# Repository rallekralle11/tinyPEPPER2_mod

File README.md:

# tinyPEPPER2 -- a tiny and lightweight 4in1 BLHeli_S ESC -- 2S edition, and modified

My intent is to modify this to become a single or double ESC for compact aircraft or battlebot use.
Original is of course by https://github.com/fishpepper

This work is published under the CERN open hardware license v1.2. 
Feel free to use the design - but make sure to give proper credit 
and release all modifications under the same license! 
See LICENSE.txt for details!

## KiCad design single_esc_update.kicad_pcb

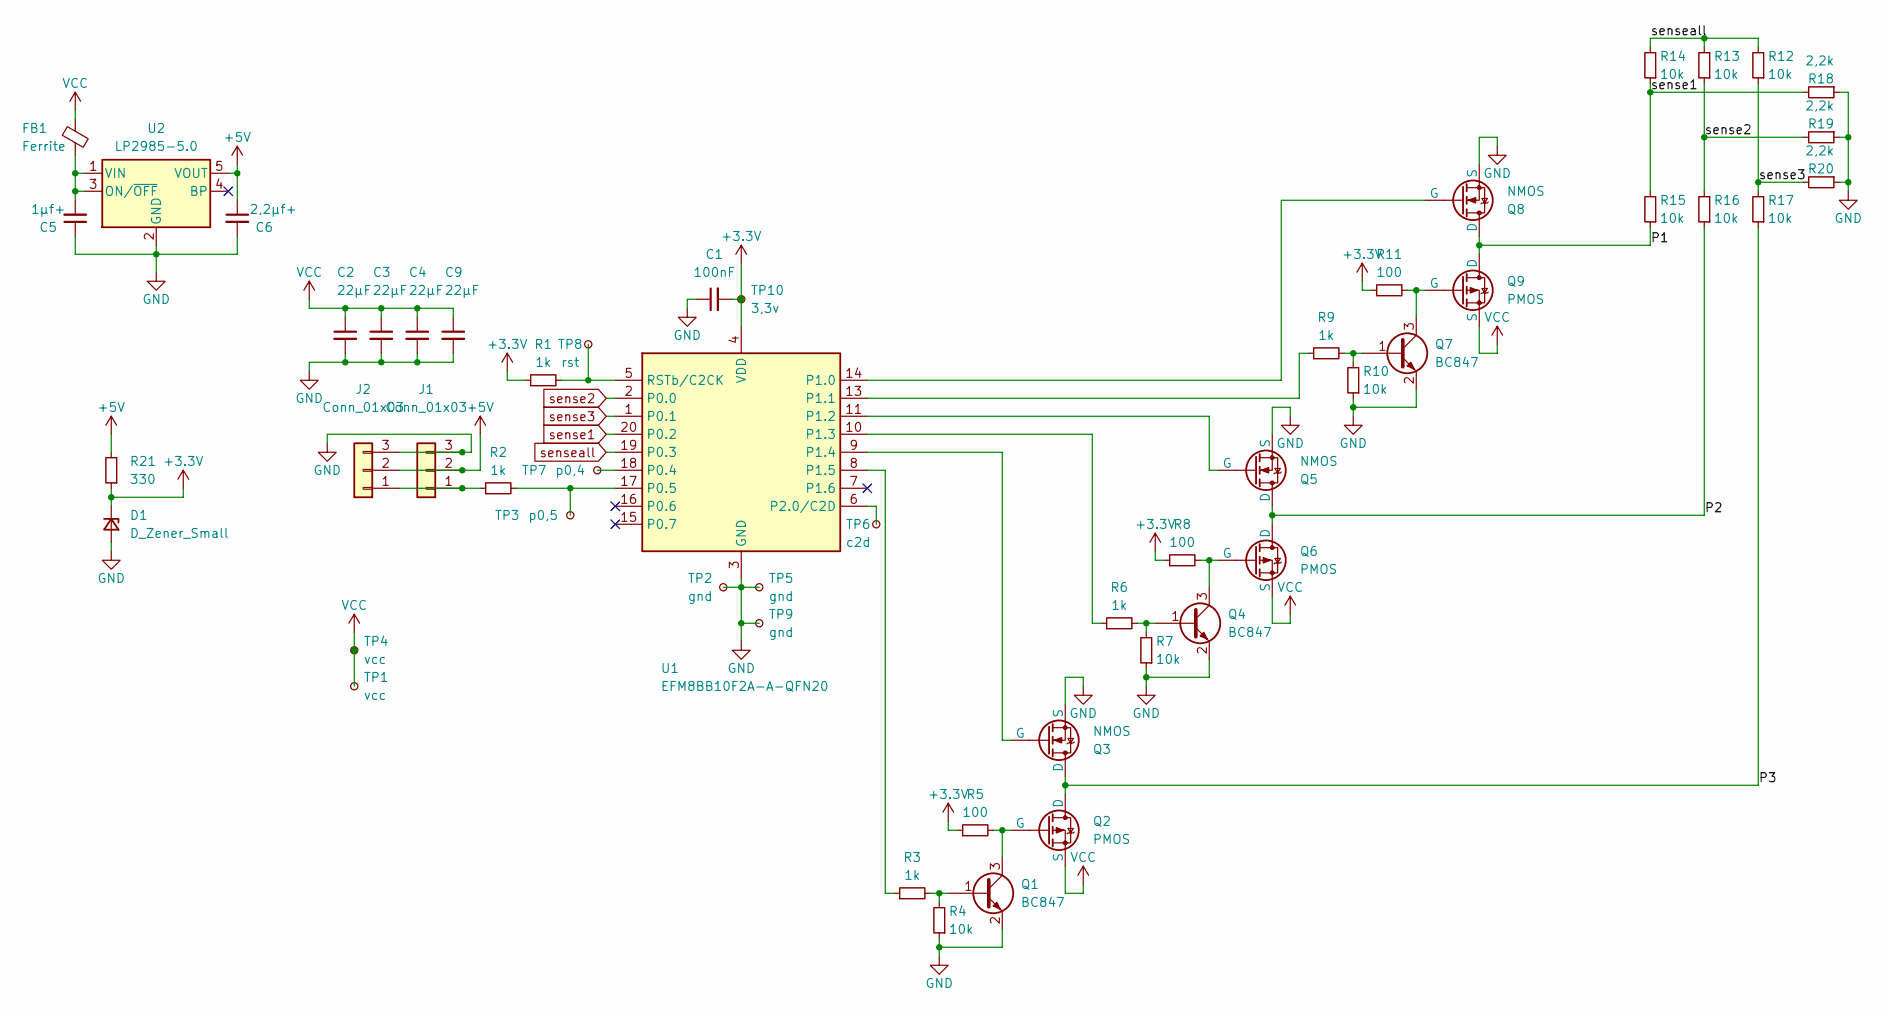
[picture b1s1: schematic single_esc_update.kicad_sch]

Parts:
C1: 100nF; C_0402_1005Metric
C2, C3, C4, C9: 22µF; C_0805_2012Metric
C5: 1µf+; C_0603_1608Metric
C6: 2,2µf+; C_0402_1005Metric
D1: D_Zener_Small; SOD323_bättre (2022_12_20 17_46_41 UTC)
FB1: Ferrite; L_0402_1005Metric
J1, J2: Conn_01x03; PinHeader_1x03_P2.54mm_Vertical
Q1, Q4, Q7: BC847; SOT-23
Q2, Q6, Q9: PMOS; DFN-8-1EP_3x3mm_P0.5mm_EP1.65x2.38mm
Q3, Q5, Q8: NMOS; DFN-8-1EP_3x3mm_P0.5mm_EP1.65x2.38mm
R1, R2, R3, R6, R9: 1k; R_0402_1005Metric
R4, R7, R10, R12, R13, R14, R15, R16, R17: 10k; R_0402_1005Metric
R5, R8, R11: 100; R_0402_1005Metric
R18, R19, R20: 2,2k; R_0402_1005Metric
R21: 330; R_0402_1005Metric
TP1, TP4: vcc; TestPoint_Pad_3.0x3.0mm
TP2, TP5: gnd; TestPoint_Pad_3.0x3.0mm
TP3: p0,5; TestPoint_Pad_D1.0mm
TP6: c2d; TestPoint_Pad_D1.0mm
TP7: p0,4; TestPoint_Pad_D1.0mm
TP8: rst; TestPoint_Pad_D1.0mm
TP9: gnd; TestPoint_Pad_D1.0mm
TP10: 3,3v; TestPoint_Pad_D1.0mm
U1: EFM8BB10F2A-A-QFN20; SiliconLabs_QFN-20-1EP_3x3mm_P0.5mm_EP1.8x1.8mm
U2: LP2985-5.0; SOT-23-5

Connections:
+3.3V: C1.2, D1.1 (K), R1.1, R5.1, R8.1, R11.1, R21.1, TP10.1, U1.4 (VDD)
+5V: C6.1, J1.2, J2.2, R21.2, U2.5 (VOUT)
/P1: Q8.1 (D), Q9.1 (D), R15.1
/P2: Q5.1 (D), Q6.1 (D), R16.1
/P3: Q2.1 (D), Q3.1 (D), R17.1
GND: C1.1, C2.2, C3.2, C4.2, C5.1, C6.2, C9.2, D1.2 (A), J1.3, J2.3, Q1.2 (E), Q3.3 (S), Q4.2 (E), Q5.3 (S), Q7.2 (E), Q8.3 (S), R4.1, R7.1, R10.1, R18.1, R19.1, R20.1, TP2.1, TP5.1, TP9.1, U1.3 (GND), U1.12 (GND), U1.21 (GND), U2.2 (GND)
unnamed: J1.1, J2.1, R2.1
unnamed: Q1.1 (B), R3.2, R4.2
unnamed: Q1.3 (C), Q2.2 (G), R5.2
unnamed: Q3.2 (G), U1.9 (P1.4)
unnamed: Q4.1 (B), R6.2, R7.2
unnamed: Q4.3 (C), Q6.2 (G), R8.2
unnamed: Q5.2 (G), U1.11 (P1.2)
unnamed: Q7.1 (B), R9.2, R10.2
unnamed: Q7.3 (C), Q9.2 (G), R11.2
unnamed: Q8.2 (G), U1.14 (P1.0)
unnamed: TP7.1, U1.18 (P0.4)
unnamed: R2.2, TP3.1, U1.17 (P0.5)
unnamed: R9.1, U1.13 (P1.1)
unnamed: R6.1, U1.10 (P1.3)
unnamed: R3.1, U1.8 (P1.5)
unnamed: TP6.1, U1.6 (P2.0/C2D)
unnamed: R1.2, TP8.1, U1.5 (RSTb/C2CK)
unnamed: C5.2, FB1.2, U2.1 (VIN), U2.3 (ON/~OFF)
VCC: C2.1, C3.1, C4.1, C9.1, FB1.1, Q2.3 (S), Q6.3 (S), Q9.3 (S), TP1.1, TP4.1
sense1: R14.1, R15.2, R18.2, U1.20 (P0.2)
sense2: R13.1, R16.2, R19.2, U1.2 (P0.0)
sense3: R12.1, R17.2, R20.2, U1.1 (P0.1)
senseall: R12.2, R13.2, R14.2, U1.19 (P0.3)

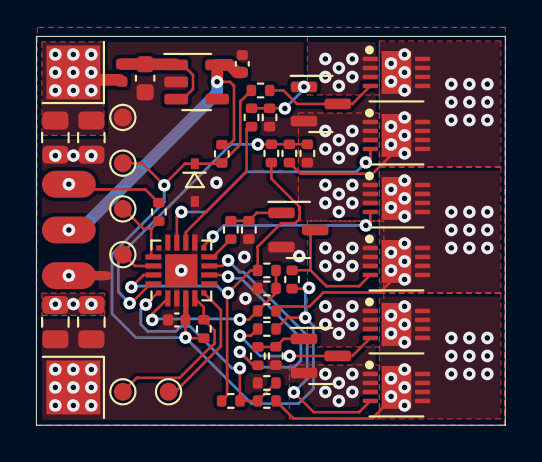
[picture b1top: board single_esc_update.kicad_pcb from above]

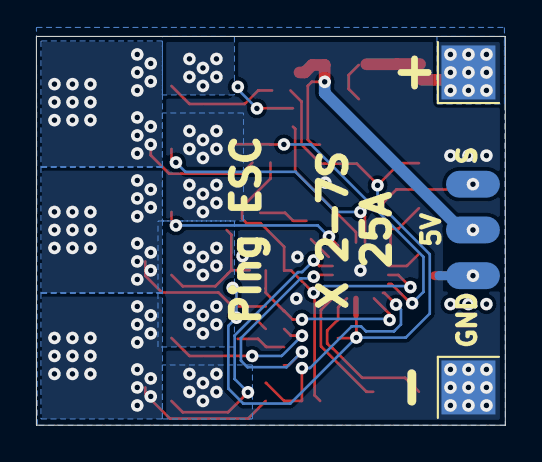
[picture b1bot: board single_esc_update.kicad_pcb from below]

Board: 4 copper layers, 26.0 x 21.6 mm, 53 parts (3 on the bottom side), 29 nets.

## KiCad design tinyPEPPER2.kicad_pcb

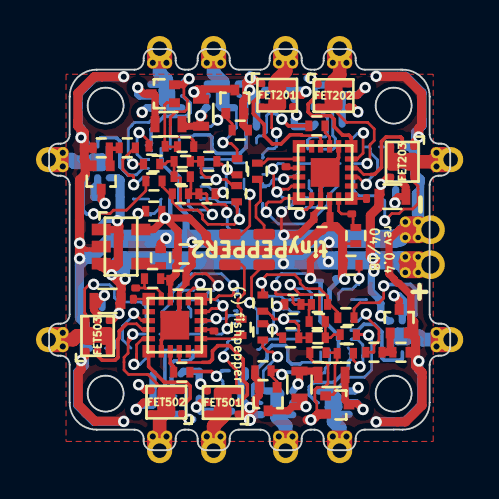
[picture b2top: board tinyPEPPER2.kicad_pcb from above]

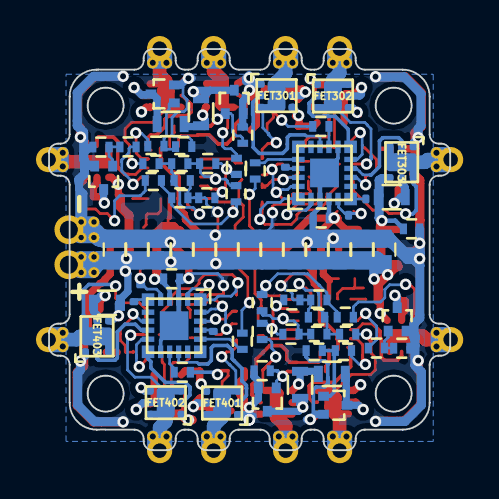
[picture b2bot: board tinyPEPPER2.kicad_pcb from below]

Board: 4 copper layers, 22.3 x 22.3 mm, 163 parts (82 on the bottom side), 100 nets.

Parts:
BL_TX201, BL_TX301, BL_TX401, BL_TX501: TP; TP_smd_0.5x0.4
C201, C301, C401, C501, C1001, C1002: 100n; C_0402_CUSTOM
C202, C203, C204, C302, C303, C304, C402, C403, C404, C502, C503, C504, C1000: 22u; C_0603_CUSTOM
C1003: 10n; C_0402_CUSTOM
FET201, FET202, FET203, FET301, FET302, FET303, FET401, FET402, FET403, FET501, FET502, FET503: UT6MA3; DFN2020-8D
H1, H2, H3, H4: hole; mouting_hole
OUT_A201, OUT_A301, OUT_A401, OUT_A501: TP; TP_PHASE_PAD
OUT_B201, OUT_B301, OUT_B401, OUT_B501: TP; TP_PHASE_PAD
OUT_C201, OUT_C301, OUT_C401, OUT_C501: TP; TP_PHASE_PAD
R201, R220, R301, R320, R401, R420, R501, R520: 1k; R_0402_CUSTOM
R202, R203, R204, R205, R206, R207, R217, R218, R219, R302, R303, R304, R305, R306, R307, R317, R318, R319, R402, R403, R404, R405, R406, R407, R417, R418, R419, R502, R503, R504, R505, R506, R507, R517, R518, R519: 10k; R_0402_CUSTOM
R208, R209, R210, R308, R309, R310, R408, R409, R410, R508, R509, R510: 2k2; R_0402_CUSTOM
R211, R212, R213, R311, R312, R313, R411, R412, R413, R511, R512, R513: 1K; R_0402_CUSTOM
R214, R215, R216, R314, R315, R316, R414, R415, R416, R514, R515, R516: 100; R_0603_CUSTOM
T201, T202, T203, T301, T302, T303, T401, T402, T403, T501, T502, T503: BC847; SC75
TP10, TP12: TP; TP_POWER_PAD_DOUBLESIDED
TP103, TP104, TP105, TP106: TP; tp_SMD_0.6x1.2
TP202, TP203, TP302, TP303, TP402, TP403, TP502, TP503: TP; TP_smd_0.5x0.4
U1: AP131-30; SOT-23-5
U201, U301, U401, U501: EFM8BB10; QFN20

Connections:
/RC_IN_0: R220.1, TP103.1
/RC_IN_1: R320.1, TP104.1
/single esc 1/3V3: C201.2, C301.2, C401.2, C501.2, C1001.1, R201.1, R301.1, R401.1, R501.1, U1.5, U201.4, U301.4, U401.4, U501.4
/single esc 1/Ac_0: R211.2, U201.13
/single esc 1/Ap_0: FET201.2, U201.14
/single esc 1/Bc_0: R212.2, U201.10
/single esc 1/Bp_0: FET202.2, U201.11
/single esc 1/C2CK_0: R201.2, TP203.1, U201.5
/single esc 1/C2D_0: TP202.1, U201.6
/single esc 1/PHASE_A_0: FET201.3, FET201.6, FET201.7, FET201.8, OUT_A201.1, R203.2
/single esc 1/PHASE_B_0: FET202.3, FET202.6, FET202.7, FET202.8, OUT_B201.1, R205.2
/single esc 1/PHASE_C_0: FET203.3, FET203.6, FET203.7, FET203.8, OUT_C201.1, R207.2
/single esc 2/Ac_0: R311.2, U301.13
/single esc 2/Ap_0: FET301.2, U301.14
/single esc 2/Bc_0: R312.2, U301.10
/single esc 2/Bp_0: FET302.2, U301.11
/single esc 2/C2CK_0: R301.2, TP303.1, U301.5
/single esc 2/C2D_0: TP302.1, U301.6
/single esc 2/PHASE_A_0: FET301.3, FET301.6, FET301.7, FET301.8, OUT_A301.1, R303.2
/single esc 2/PHASE_B_0: FET302.3, FET302.6, FET302.7, FET302.8, OUT_B301.1, R305.2
/single esc 2/PHASE_C_0: FET303.3, FET303.6, FET303.7, FET303.8, OUT_C301.1, R307.2
/single esc 3/Ac_0: R411.2, U401.13
/single esc 3/Ap_0: FET401.2, U401.14
/single esc 3/Bc_0: R412.2, U401.10
/single esc 3/Bp_0: FET402.2, U401.11
/single esc 3/C2CK_0: R401.2, TP403.1, U401.5
/single esc 3/C2D_0: TP402.1, U401.6
/single esc 3/PHASE_A_0: FET401.3, FET401.6, FET401.7, FET401.8, OUT_A401.1, R403.2
/single esc 3/PHASE_B_0: FET402.3, FET402.6, FET402.7, FET402.8, OUT_B401.1, R405.2
/single esc 3/PHASE_C_0: FET403.3, FET403.6, FET403.7, FET403.8, OUT_C401.1, R407.2
/single esc 3/RC_IN: R420.1, TP105.1
/single esc 4/Ac_0: R511.2, U501.13
/single esc 4/Ap_0: FET501.2, U501.14
/single esc 4/Bc_0: R512.2, U501.10
/single esc 4/Bp_0: FET502.2, U501.11
/single esc 4/C2CK_0: R501.2, TP503.1, U501.5
/single esc 4/C2D_0: TP502.1, U501.6
/single esc 4/PHASE_A_0: FET501.3, FET501.6, FET501.7, FET501.8, OUT_A501.1, R503.2
/single esc 4/PHASE_B_0: FET502.3, FET502.6, FET502.7, FET502.8, OUT_B501.1, R505.2
/single esc 4/PHASE_C_0: FET503.3, FET503.6, FET503.7, FET503.8, OUT_C501.1, R507.2
/single esc 4/RC_IN: R520.1, TP106.1
GND: C201.1, C202.1, C203.1, C204.1, C301.1, C302.1, C303.1, C304.1, C401.1, C402.1, C403.1, C404.1, C501.1, C502.1, C503.1, C504.1, C1000.1, C1001.2, C1002.2, C1003.2, FET201.1, FET202.1, FET203.1, FET301.1, FET302.1, FET303.1, FET401.1, FET402.1, FET403.1, FET501.1, FET502.1, FET503.1, R208.1, R209.1, R210.1, R217.1, R218.1, R219.1, R308.1, R309.1, R310.1, R317.1, R318.1, R319.1, R408.1, R409.1, R410.1, R417.1, R418.1, R419.1, R508.1, R509.1, R510.1, R517.1, R518.1, R519.1, T201.2, T202.2, T203.2, T301.2, T302.2, T303.2, T401.2, T402.2, T403.2, T501.2, T502.2, T503.2, TP12.1, U1.2, U201.3, U201.12, U201.21, U301.3, U301.12, U301.21, U401.3, U401.12, U401.21, U501.3, U501.12, U501.21
unnamed: BL_TX201.1, U201.18
unnamed: BL_TX301.1, U301.18
unnamed: BL_TX401.1, U401.18
unnamed: BL_TX501.1, U501.18
unnamed: C1003.1, U1.4
unnamed: FET201.5, R214.2, T201.3
unnamed: FET202.5, R215.2, T202.3
unnamed: FET203.2, U201.9
unnamed: FET203.5, R216.2, T203.3
unnamed: FET301.5, R314.2, T301.3
unnamed: FET302.5, R315.2, T302.3
unnamed: FET303.2, U301.9
unnamed: FET303.5, R316.2, T303.3
unnamed: FET401.5, R414.2, T401.3
unnamed: FET402.5, R415.2, T402.3
unnamed: FET403.2, U401.9
unnamed: FET403.5, R416.2, T403.3
unnamed: FET501.5, R514.2, T501.3
unnamed: FET502.5, R515.2, T502.3
unnamed: FET503.2, U501.9
unnamed: FET503.5, R516.2, T503.3
unnamed: R202.1, R204.1, R206.1, U201.19
unnamed: R202.2, R203.1, R208.2, U201.20
unnamed: R204.2, R205.1, R209.2, U201.2
unnamed: R206.2, R207.1, R210.2, U201.1
unnamed: R211.1, R217.2, T201.1
unnamed: R212.1, R218.2, T202.1
unnamed: R213.1, R219.2, T203.1
unnamed: R213.2, U201.8
unnamed: R220.2, U201.17
unnamed: R302.1, R304.1, R306.1, U301.19
unnamed: R302.2, R303.1, R308.2, U301.20
unnamed: R304.2, R305.1, R309.2, U301.2
unnamed: R306.2, R307.1, R310.2, U301.1
unnamed: R311.1, R317.2, T301.1
unnamed: R312.1, R318.2, T302.1
unnamed: R313.1, R319.2, T303.1
unnamed: R313.2, U301.8
unnamed: R320.2, U301.17
unnamed: R402.1, R404.1, R406.1, U401.19
unnamed: R402.2, R403.1, R408.2, U401.20
unnamed: R404.2, R405.1, R409.2, U401.2
unnamed: R406.2, R407.1, R410.2, U401.1
unnamed: R411.1, R417.2, T401.1
unnamed: R412.1, R418.2, T402.1
unnamed: R413.1, R419.2, T403.1
unnamed: R413.2, U401.8
unnamed: R420.2, U401.17
unnamed: R502.1, R504.1, R506.1, U501.19
unnamed: R502.2, R503.1, R508.2, U501.20
unnamed: R504.2, R505.1, R509.2, U501.2
unnamed: R506.2, R507.1, R510.2, U501.1
unnamed: R511.1, R517.2, T501.1
unnamed: R512.1, R518.2, T502.1
unnamed: R513.1, R519.2, T503.1
unnamed: R513.2, U501.8
unnamed: R520.2, U501.17
VCC: C202.2, C203.2, C204.2, C302.2, C303.2, C304.2, C402.2, C403.2, C404.2, C502.2, C503.2, C504.2, C1000.2, C1002.1, FET201.4, FET202.4, FET203.4, FET301.4, FET302.4, FET303.4, FET401.4, FET402.4, FET403.4, FET501.4, FET502.4, FET503.4, R214.1, R215.1, R216.1, R314.1, R315.1, R316.1, R414.1, R415.1, R416.1, R514.1, R515.1, R516.1, TP10.1, U1.1, U1.3

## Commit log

2023-11-22 got it working in kicad7
2023-11-22 ok now it works in 7. i think
2023-11-24 made a new schematic with individual FETs
2023-12-22 forget
